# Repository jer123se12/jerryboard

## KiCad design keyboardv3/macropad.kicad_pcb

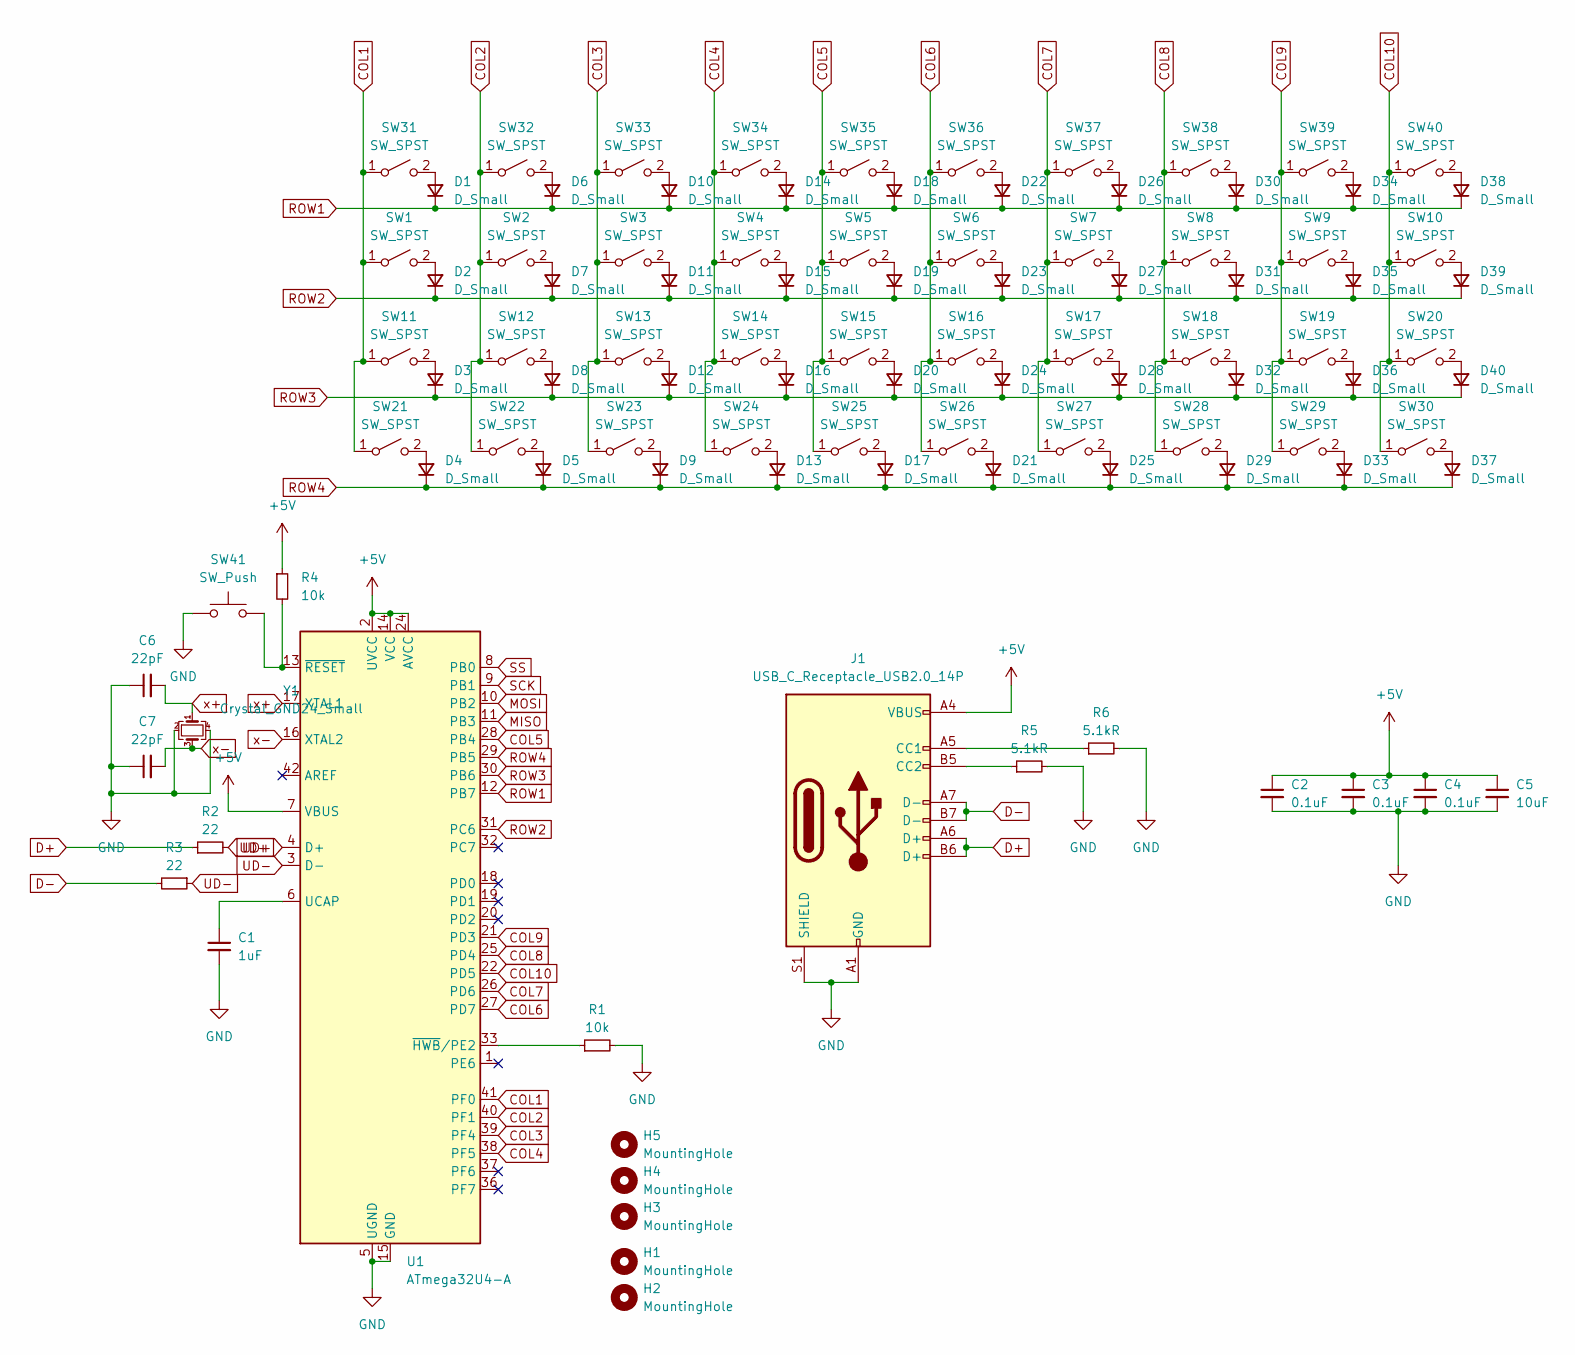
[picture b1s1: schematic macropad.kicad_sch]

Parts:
C1: 1uF; C_0805_2012Metric_Pad1.18x1.45mm_HandSolder
C2, C3, C4: 0.1uF; C_0805_2012Metric_Pad1.18x1.45mm_HandSolder
C5: 10uF; C_0805_2012Metric_Pad1.18x1.45mm_HandSolder
C6, C7: 22pF; C_0805_2012Metric_Pad1.18x1.45mm_HandSolder
D1, D2, D3, D4, D5, D6, D7, D8, D9, D10, D11, D12, D13, D14, D15, D16, D17, D18, D19, D20, D21, D22, D23, D24, D25, D26, D27, D28, D29, D30, D31, D32, D33, D34, D35, D36, D37, D38, D39, D40: D_Small; D_SOD-123
H1, H2, H3, H4, H5: MountingHole; MountingHole_2.7mm_M2.5
J1: USB_C_Receptacle_USB2.0_14P; USB_C_Receptacle_HRO_TYPE-C-31-M-12
R1, R4: 10k; R_0805_2012Metric_Pad1.20x1.40mm_HandSolder
R2, R3: 22; R_0805_2012Metric_Pad1.20x1.40mm_HandSolder
R5, R6: 5.1kR; R_0805_2012Metric_Pad1.20x1.40mm_HandSolder
SW1, SW2, SW3, SW4, SW5, SW6, SW7, SW8, SW9, SW10, SW11, SW12, SW13, SW14, SW15, SW16, SW17, SW18, SW19, SW20, SW21, SW22, SW23, SW24, SW25, SW26, SW27, SW28, SW29, SW30, SW31, SW32, SW33, SW34, SW35, SW36, SW37, SW38, SW39, SW40: SW_SPST; SW_Kailh_Choc_V1
SW41: SW_Push; C_0805_2012Metric_Pad1.18x1.45mm_HandSolder
U1: ATmega32U4-A; TQFP-44_10x10mm_P0.8mm
Y1: Crystal_GND24_Small; Crystal_SMD_3225-4Pin_3.2x2.5mm_HandSoldering

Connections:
+5V: C2.1, C3.1, C4.1, C5.1, J1.A4 (VBUS), J1.A9 (VBUS), J1.B4 (VBUS), J1.B9 (VBUS), R4.1, U1.2 (UVCC), U1.7 (VBUS), U1.14 (VCC), U1.24 (AVCC), U1.34 (VCC), U1.44 (AVCC)
COL1: SW1.1 (A), SW11.1 (A), SW21.1 (A), SW31.1 (A), U1.41 (PF0)
COL2: SW2.1 (A), SW12.1 (A), SW22.1 (A), SW32.1 (A), U1.40 (PF1)
COL3: SW3.1 (A), SW13.1 (A), SW23.1 (A), SW33.1 (A), U1.39 (PF4)
COL4: SW4.1 (A), SW14.1 (A), SW24.1 (A), SW34.1 (A), U1.38 (PF5)
COL5: SW5.1 (A), SW15.1 (A), SW25.1 (A), SW35.1 (A), U1.28 (PB4)
COL6: SW6.1 (A), SW16.1 (A), SW26.1 (A), SW36.1 (A), U1.27 (PD7)
COL7: SW7.1 (A), SW17.1 (A), SW27.1 (A), SW37.1 (A), U1.26 (PD6)
COL8: SW8.1 (A), SW18.1 (A), SW28.1 (A), SW38.1 (A), U1.25 (PD4)
COL9: SW9.1 (A), SW19.1 (A), SW29.1 (A), SW39.1 (A), U1.21 (PD3)
COL10: SW10.1 (A), SW20.1 (A), SW30.1 (A), SW40.1 (A), U1.22 (PD5)
D+: J1.A6 (D+), J1.B6 (D+), R2.1
D-: J1.A7 (D-), J1.B7 (D-), R3.2
GND: C1.2, C2.2, C3.2, C4.2, C5.2, C6.1, C7.1, J1.A1 (GND), J1.A12 (GND), J1.B1 (GND), J1.B12 (GND), J1.S1 (SHIELD), R1.2, R5.2, R6.2, SW41.1, U1.5 (UGND), U1.15 (GND), U1.23 (GND), U1.35 (GND), U1.43 (GND), Y1.2, Y1.4
MISO: U1.11 (PB3)
MOSI: U1.10 (PB2)
unnamed: D1.2 (A), SW31.2 (B)
unnamed: D2.2 (A), SW1.2 (B)
unnamed: D3.2 (A), SW11.2 (B)
unnamed: D4.2 (A), SW21.2 (B)
unnamed: D5.2 (A), SW22.2 (B)
unnamed: D6.2 (A), SW32.2 (B)
unnamed: D7.2 (A), SW2.2 (B)
unnamed: D8.2 (A), SW12.2 (B)
unnamed: D9.2 (A), SW23.2 (B)
unnamed: D10.2 (A), SW33.2 (B)
unnamed: D11.2 (A), SW3.2 (B)
unnamed: D12.2 (A), SW13.2 (B)
unnamed: D13.2 (A), SW24.2 (B)
unnamed: D14.2 (A), SW34.2 (B)
unnamed: D15.2 (A), SW4.2 (B)
unnamed: D16.2 (A), SW14.2 (B)
unnamed: D17.2 (A), SW25.2 (B)
unnamed: D18.2 (A), SW35.2 (B)
unnamed: D19.2 (A), SW5.2 (B)
unnamed: D20.2 (A), SW15.2 (B)
unnamed: D21.2 (A), SW26.2 (B)
unnamed: D22.2 (A), SW36.2 (B)
unnamed: D23.2 (A), SW6.2 (B)
unnamed: D24.2 (A), SW16.2 (B)
unnamed: D25.2 (A), SW27.2 (B)
unnamed: D26.2 (A), SW37.2 (B)
unnamed: D27.2 (A), SW7.2 (B)
unnamed: D28.2 (A), SW17.2 (B)
unnamed: D29.2 (A), SW28.2 (B)
unnamed: D30.2 (A), SW38.2 (B)
unnamed: D31.2 (A), SW8.2 (B)
unnamed: D32.2 (A), SW18.2 (B)
unnamed: D33.2 (A), SW29.2 (B)
unnamed: D34.2 (A), SW39.2 (B)
unnamed: D35.2 (A), SW9.2 (B)
unnamed: D36.2 (A), SW19.2 (B)
unnamed: D37.2 (A), SW30.2 (B)
unnamed: D38.2 (A), SW40.2 (B)
unnamed: D39.2 (A), SW10.2 (B)
unnamed: D40.2 (A), SW20.2 (B)
unnamed: J1.A5 (CC1), R6.1
unnamed: J1.B5 (CC2), R5.1
unnamed: C1.1, U1.6 (UCAP)
unnamed: R1.1, U1.33 (~HWB/PE2)
unnamed: R4.2, SW41.2, U1.13 (~RESET)
ROW1: D1.1 (K), D6.1 (K), D10.1 (K), D14.1 (K), D18.1 (K), D22.1 (K), D26.1 (K), D30.1 (K), D34.1 (K), D38.1 (K), U1.12 (PB7)
ROW2: D2.1 (K), D7.1 (K), D11.1 (K), D15.1 (K), D19.1 (K), D23.1 (K), D27.1 (K), D31.1 (K), D35.1 (K), D39.1 (K), U1.31 (PC6)
ROW3: D3.1 (K), D8.1 (K), D12.1 (K), D16.1 (K), D20.1 (K), D24.1 (K), D28.1 (K), D32.1 (K), D36.1 (K), D40.1 (K), U1.30 (PB6)
ROW4: D4.1 (K), D5.1 (K), D9.1 (K), D13.1 (K), D17.1 (K), D21.1 (K), D25.1 (K), D29.1 (K), D33.1 (K), D37.1 (K), U1.29 (PB5)
SCK: U1.9 (PB1)
SS: U1.8 (PB0)
UD+: R2.2, U1.4 (D+)
UD-: R3.1, U1.3 (D-)
x+: C6.2, U1.17 (XTAL1), Y1.1
x-: C7.2, U1.16 (XTAL2), Y1.3

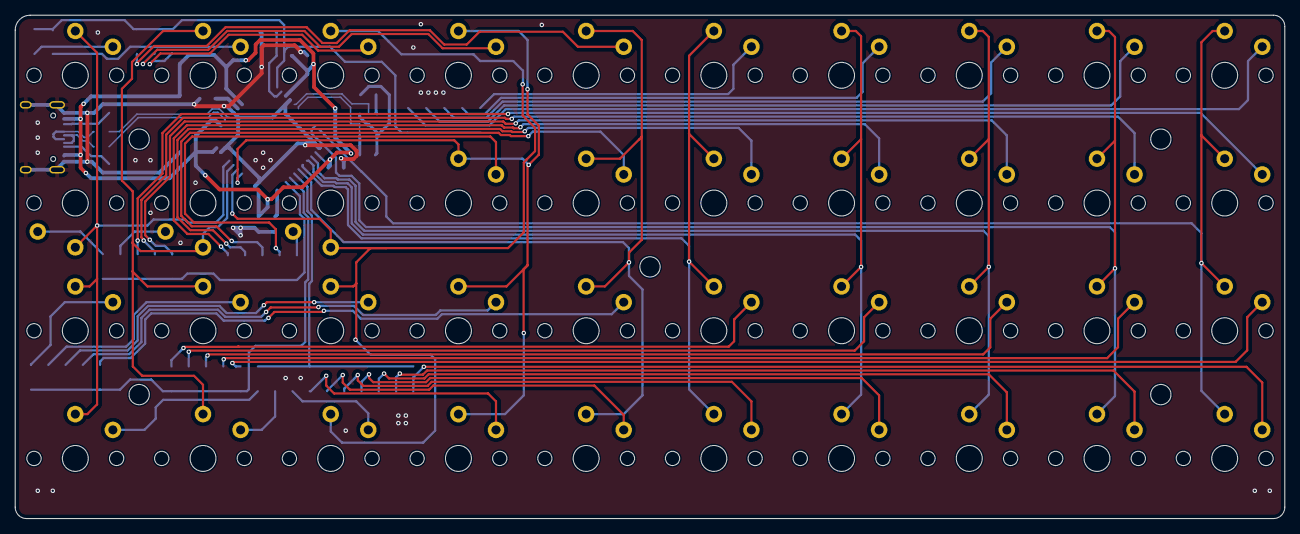
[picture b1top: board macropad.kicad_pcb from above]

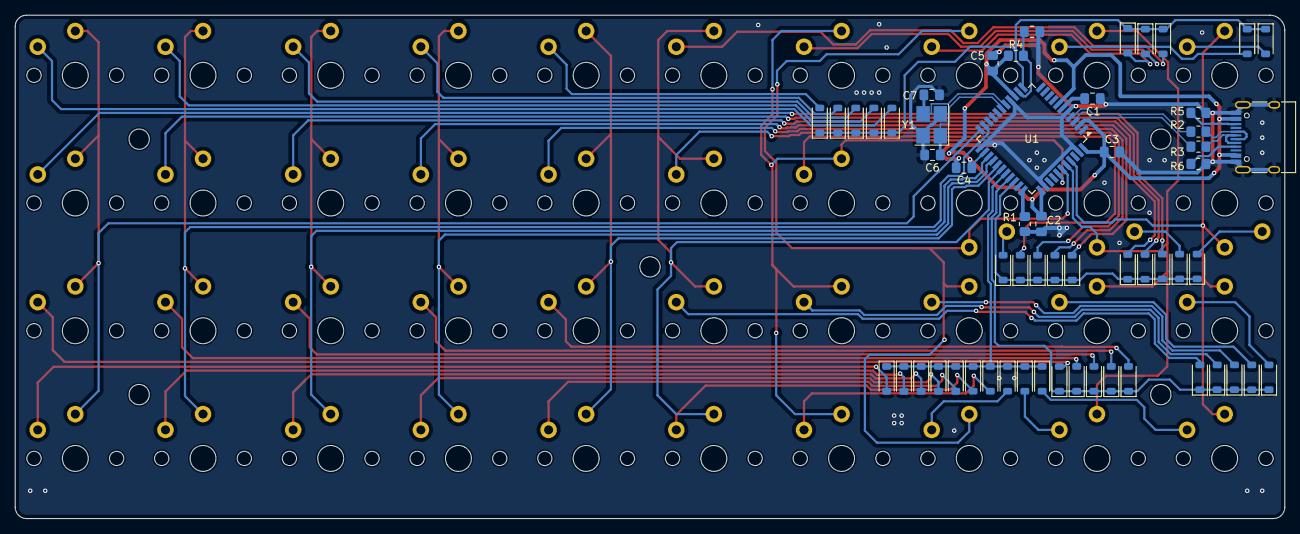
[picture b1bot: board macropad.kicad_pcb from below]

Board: 2 copper layers, 169.0 x 67.0 mm, 102 parts (57 on the bottom side), 67 nets.

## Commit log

2025-05-01 inital commit
2025-05-09 aaaa mx
2025-05-21 finished routes
